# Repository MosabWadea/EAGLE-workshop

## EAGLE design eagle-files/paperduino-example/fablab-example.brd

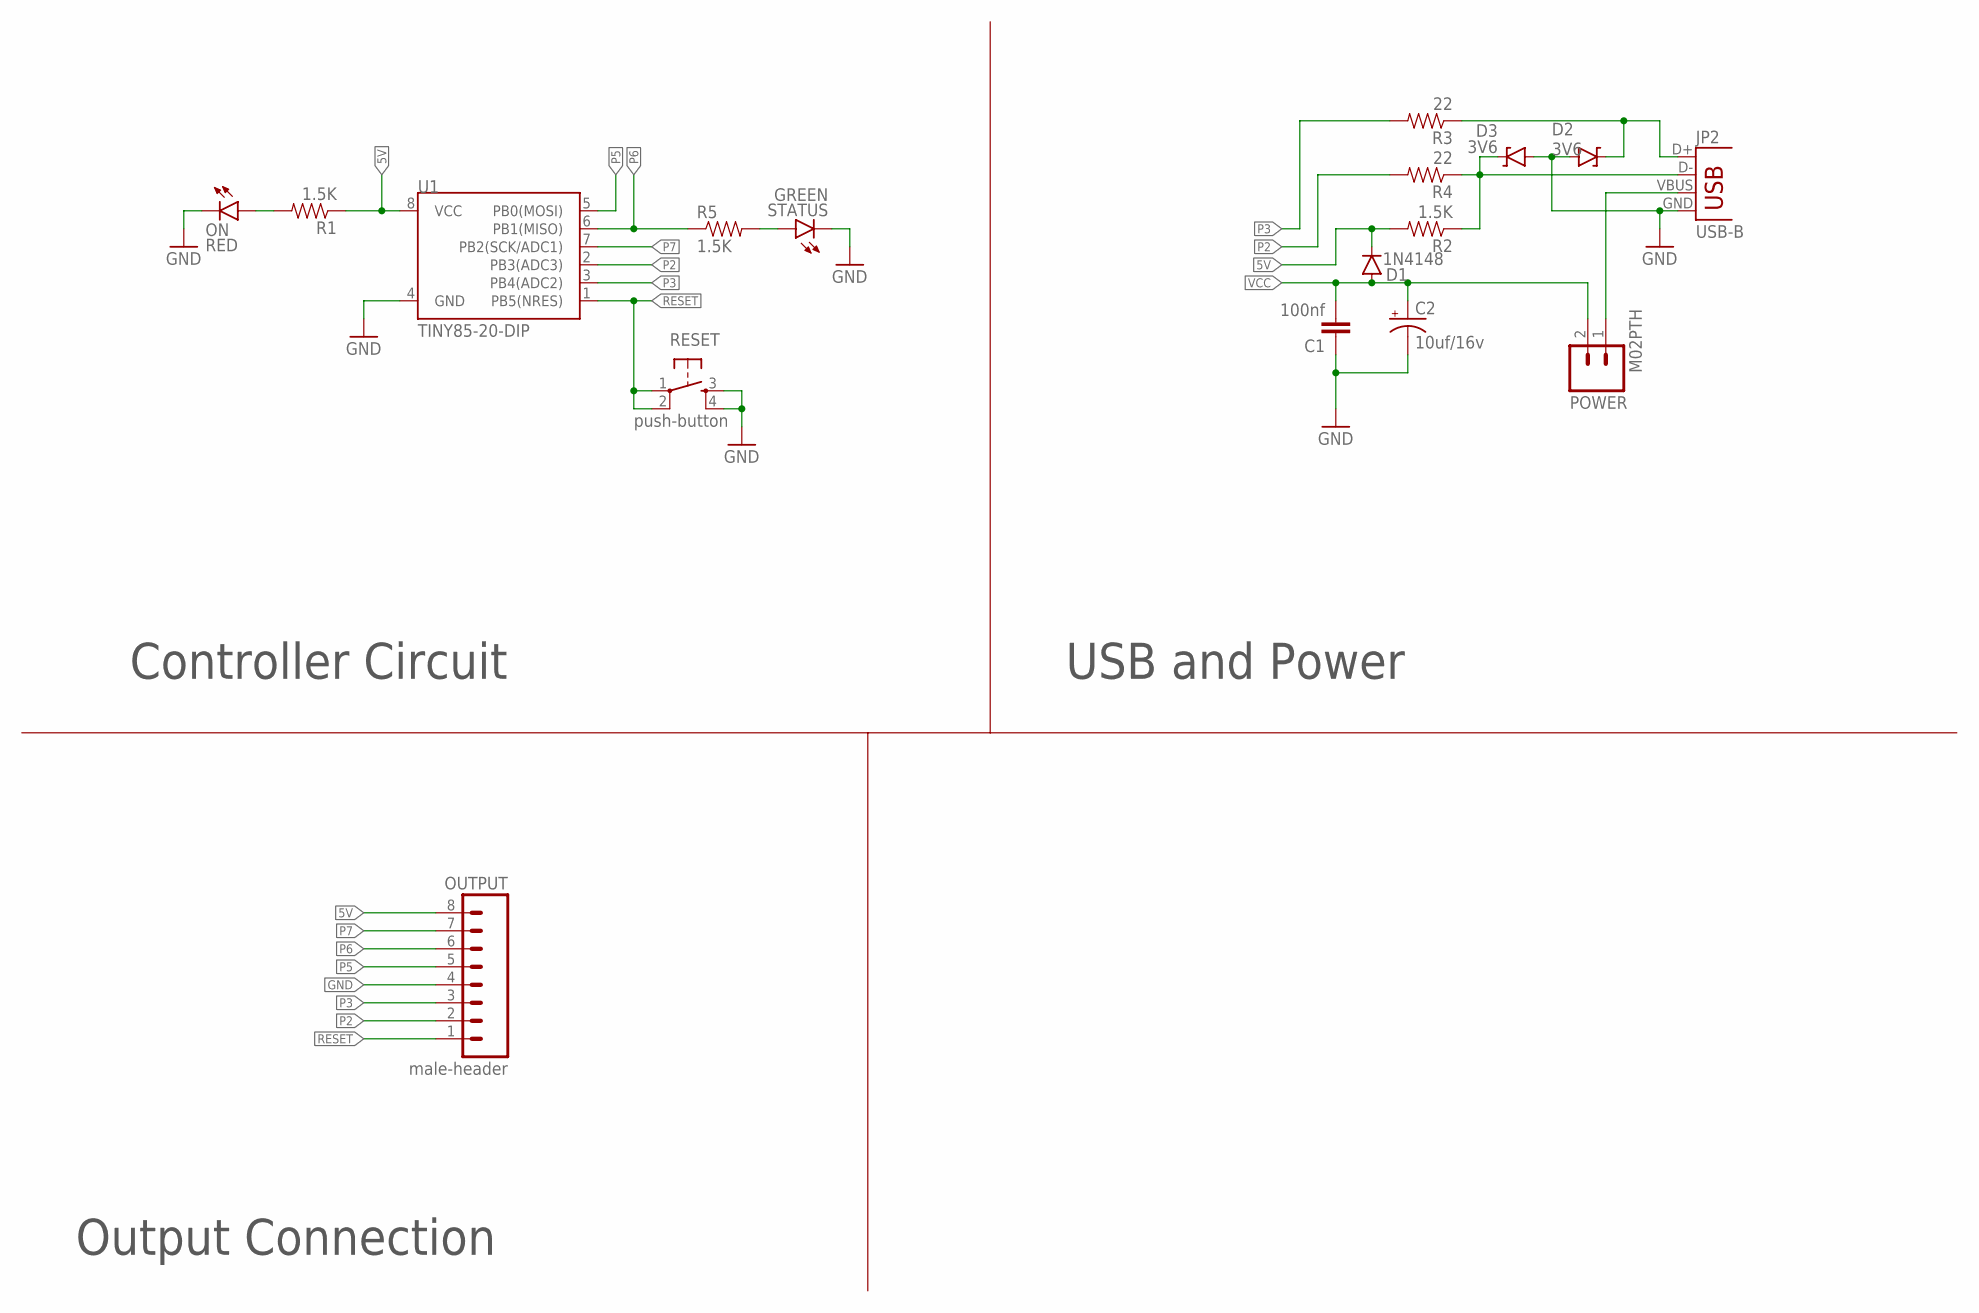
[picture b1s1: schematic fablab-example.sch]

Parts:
C1: 100nf; CAP-PTH-SMALL
C2: 10uf/16v; CPOL-RADIAL-10UF-25V
D1: 1N4148; DIODE-1N4148
D2, D3: 3V6; DIODE-ZENER
JP2: USB-B; USB-B-PTH
ON: RED; LED3MM
OUTPUT: male-header; 1X08_ROUND
POWER: M02PTH; 1X02
R1, R2, R5: 1.5K; 1206
R3, R4: 22; 1206
RESET: push-button; TACTILE-PTH
STATUS: GREEN; LED3MM
U1: TINY85-20-DIP; DIP08

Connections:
5V: D1.C, OUTPUT.8, R1.1, R2.2, U1.8 (VCC)
GND: C1.1, C2.2 (-), D2.P$2 (A), D3.P$2 (A), JP2.GND, ON.K (C), OUTPUT.4, RESET.3, RESET.4, STATUS.K (C), U1.4 (GND)
unnamed: ON.A, R1.2
unnamed: R5.2, STATUS.A
unnamed: D2.P$1 (C), JP2.D+, R3.1
unnamed: D3.P$1 (C), JP2.D-, R2.1, R4.1
unnamed: JP2.VBUS, POWER.1
P2: OUTPUT.2, R4.2, U1.2 (PB3(ADC3))
P3: OUTPUT.3, R3.2, U1.3 (PB4(ADC2))
P5: OUTPUT.5, U1.5 (PB0(MOSI))
P6: OUTPUT.6, R5.1, U1.6 (PB1(MISO))
P7: OUTPUT.7, U1.7 (PB2(SCK/ADC1))
RESET: OUTPUT.1, RESET.1, RESET.2, U1.1 (PB5(NRES))
VCC: C1.2, C2.1 (+), D1.A, POWER.2

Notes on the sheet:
Controller Circuit
USB and Power
Output Connection

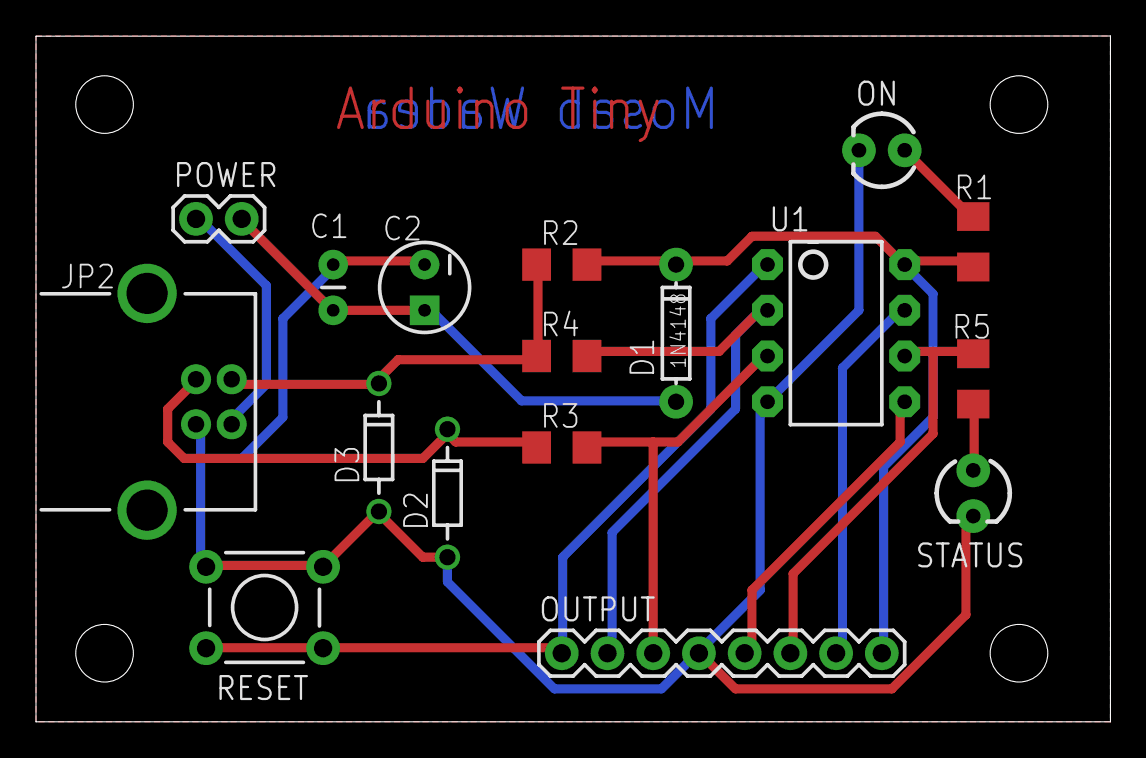
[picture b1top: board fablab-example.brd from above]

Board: 2 copper layers, 59.7 x 38.1 mm, 18 parts (0 on the bottom side), 14 nets.

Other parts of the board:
_REFERENCE_HOLE_: _REFERENCE_HOLE_

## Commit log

2015-07-16 added files

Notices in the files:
parts and their libraries:
SparkFun-Capacitors: Licensing: Creative Commons ShareAlike 4.0 International - https://creativecommons.org/licenses/by-sa/4.0
